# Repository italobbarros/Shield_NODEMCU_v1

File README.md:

# Shield_NODEMCU_v1
Projeto de shield para o esp 8266 nodemcu

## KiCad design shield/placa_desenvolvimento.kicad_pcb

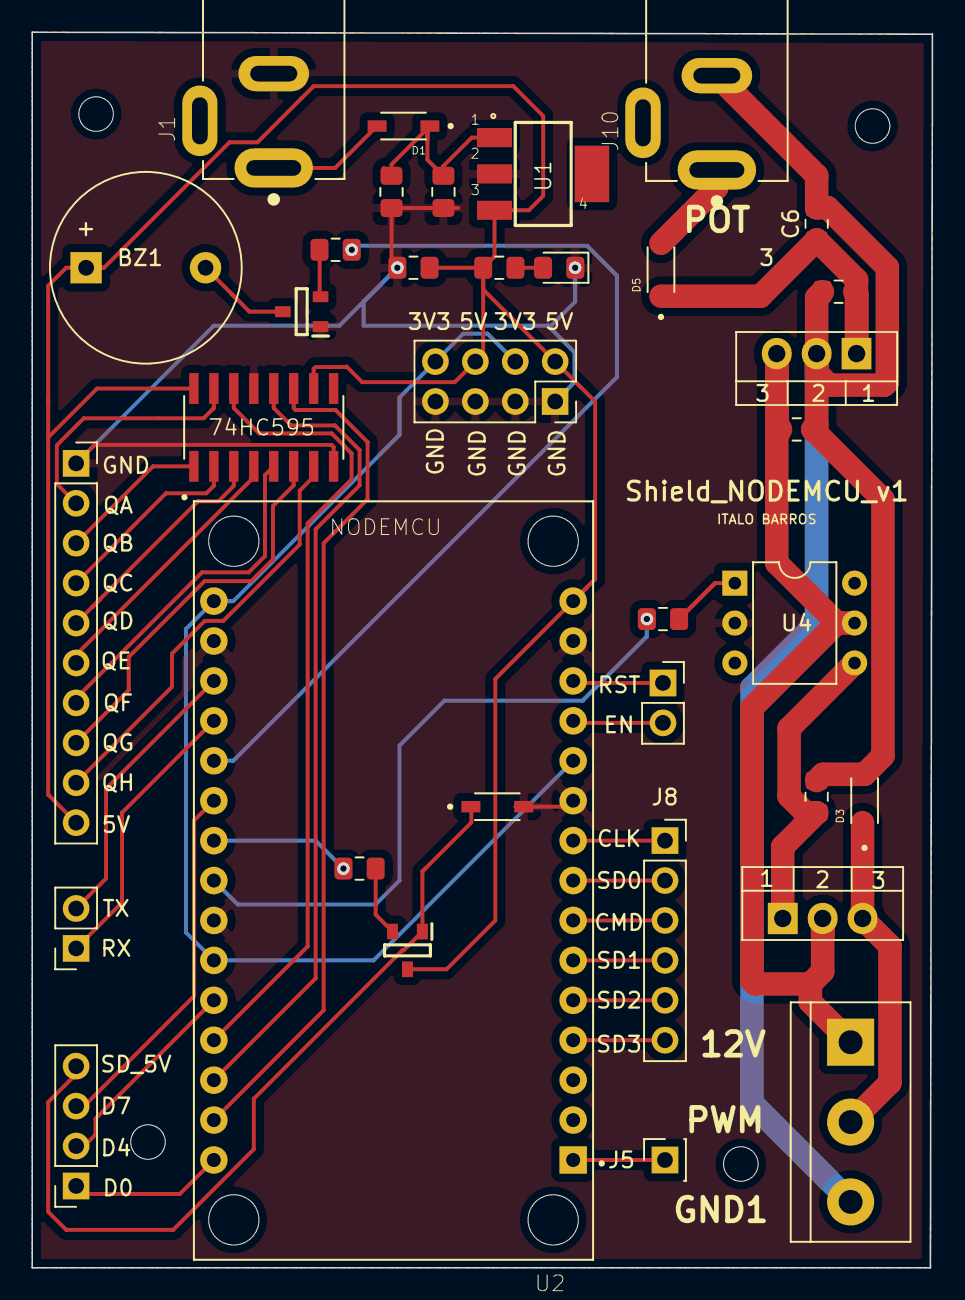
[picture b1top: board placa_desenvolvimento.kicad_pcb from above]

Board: 2 copper layers, 57.3 x 78.6 mm, 35 parts (0 on the bottom side), 45 nets.

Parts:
BZ1: Buzzer; Buzzer_12x9.5RM7.6
C1, C2, C5, C6: 100n; C_0805_2012Metric_Pad1.15x1.40mm_HandSolder
C3: 10n; C_0805_2012Metric_Pad1.15x1.40mm_HandSolder
C4: 330n; C_0805_2012Metric_Pad1.15x1.40mm_HandSolder
D1, D5: BAT60J; 1N5819HW-7-F
D2: LED; LED_0805_2012Metric_Pad1.15x1.40mm_HandSolder
D3, D4: 1N4007; 1N5819HW-7-F
J1, J10: Jack-DC; CUI_PJ-002A
J2: Saida para rele; PinSocket_1x10_P2.54mm_Vertical
J3: saidas digitais; PinSocket_1x04_P2.54mm_Vertical
J4, J6: Conn_01x02_Male; PinSocket_1x02_P2.54mm_Vertical
J5: Conn_01x01_Male; PinSocket_1x01_P2.54mm_Vertical
J7: born; TerminalBlock_bornier-3_P5.08mm
J8: Conn_01x06_Male; PinSocket_1x06_P2.54mm_Vertical
J9: Conn_02x04_Odd_Even; PinSocket_2x04_P2.54mm_Vertical
Q1, Q5: 2N2222; SOT95P240X120-3N
Q2: IRF640; TO-220-3_Vertical
R1: 220; R_0805_2012Metric_Pad1.15x1.40mm_HandSolder
R2, R8: 2k2; R_0805_2012Metric_Pad1.15x1.40mm_HandSolder
R3: 150; R_0805_2012Metric_Pad1.15x1.40mm_HandSolder
R4: 10k; R_0805_2012Metric_Pad1.15x1.40mm_HandSolder
U1: ld1117_5v; SOT223
U2: NODEMCU; MODULE_ZC563900
U3: LM7812_TO220; TO-220-3_Vertical
U4: 4N25; DIP-6_W7.62mm
U601: 74HC595; SOIC127P600X175-16N

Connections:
+3V3: J9.4, J9.8, U2.11, U2.16, U2.25
+5V: BZ1.1, C3.1, J2.10, J9.2, J9.6, Q5.3, R1.2, U1.3, U2.15, U601.10, U601.16
+12V: C5.1, J7.1, Q2.2, U3.3, U4.5
A0: J5.1, U2.1
CLK: J8.1, U2.9
CMD: J8.3, U2.7
D0: J3.1, U2.30
D4: J3.2, U2.26
D5: R3.2, U2.23
D6: R8.2, U2.22
D7: J3.3, U2.21
EN: J4.2, U2.12
GND: C1.2, C2.2, C3.2, D2.1, D4.2, J1.2, J2.1, J9.1, J9.3, J9.5, J9.7, Q1.1, U1.2, U2.10, U2.14, U2.17, U2.24, U4.2, U601.8, U601.13
GND1: C4.2, C5.2, C6.2, D3.2, J7.3, J10.2, R4.1, U3.2
unnamed: BZ1.2, Q1.3
unnamed: D1.2, J1.1
unnamed: D2.2, R1.1
unnamed: D5.2, J10.1
unnamed: Q1.2, R2.1
unnamed: Q2.1, R4.2, U4.4
unnamed: Q5.2, R8.1
unnamed: R3.1, U4.1
PEN: U2.28, U601.12
PWM: R2.2, U2.20
QA: J2.2, U601.15
QB: J2.3, U601.1
QC: J2.4, U601.2
QD: J2.5, U601.3
QE: J2.6, U601.4
QF: J2.7, U601.5
QG: J2.8, U601.6
QH: J2.9, U601.7
RST: J4.1, U2.13
RX: J6.1, U2.19
SD0: J8.2, U2.8
SD1: J8.4, U2.6
SD2: J8.5, U2.5
SD3: J8.6, U2.4
SD_5V: D4.1, J3.4, Q5.1
SD_12V: D3.1, J7.2, Q2.3
SOCLK: U2.29, U601.11
SODATA: U2.27, U601.14
TX: J6.2, U2.18
VCC: C1.1, C2.1, D1.1, U1.1
VCCQ: C4.1, C6.1, D5.1, U3.1

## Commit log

2020-07-30 v1
    V1 com MQTT dos 8 reles controlado pelo registrador de deslocamento
2020-07-30 v1
    V1 MQTT com esp8266 e 8 rele controlado pelo 74hc595
2020-07-30 Desenvolvimento da pcb v1
    Desenvolvimento v1 da shield que será utilizada com o esp nodemcu para projeto de automação residencial
2020-07-30 Revert "Merge branch 'master' of https://github.com/italobbarros/Shield_NODEMCU_v1"
    This reverts commit ff37a9c58489a60c12a5bacb6b9c39a05d01b0f3, reversing
    changes made to 8b9b7b1ff0056f9df544eae667b6f23f110dc824.
2020-07-30 Revert "Revert "Merge branch 'master' of https://github.com/italobbarros/Shield_NODEMCU_v1""
    This reverts commit 6dfe11520a630042a4d8e57a25e4fc06cd3a202b.
2020-07-30 Desenvolvimento shield v1
2020-07-30 Desenvolvimento da pcb v1
2020-07-30 update v1
2020-08-03 Server local para iot
    Server local para iot
2020-08-04 Update Server_local
    Atualização dos botões da rede local
